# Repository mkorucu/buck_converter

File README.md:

View this project on [CADLAB.io](https://cadlab.io/project/27289). 

# buck_converter

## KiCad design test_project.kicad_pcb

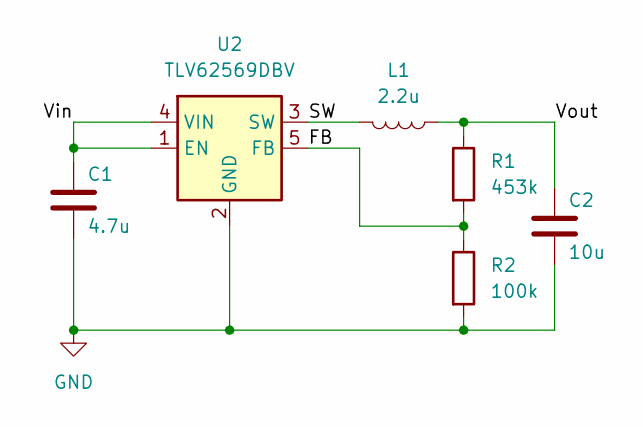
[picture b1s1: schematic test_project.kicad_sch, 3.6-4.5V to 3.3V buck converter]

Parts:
C1: 4.7u; C_0402_1005Metric
C2: 10u; C_0402_1005Metric
L1: 2.2u; L_Chilisin_BMRB00050518-B
R1: 453k; R_0402_1005Metric
R2: 100k; R_0402_1005Metric
U2: TLV62569DBV; SOT-23-5

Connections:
/FB: R1.2, R2.1, U2.5 (FB)
/SW: L1.2, U2.3 (SW)
/Vin: C1.1, U2.1 (EN), U2.4 (VIN)
/Vout: C2.1, L1.1, R1.1
GND: C1.2, C2.2, R2.2, U2.2 (GND)

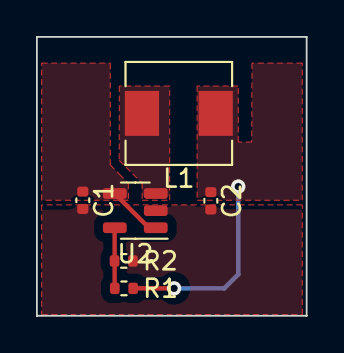
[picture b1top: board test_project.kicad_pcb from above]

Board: 2 copper layers, 15.0 x 15.5 mm, 6 parts (0 on the bottom side), 5 nets.

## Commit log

2023-09-01 Backlink to CADLAB.io has been added.
2023-09-01 little changes in schematic and layout
2023-09-06 pcb edited
